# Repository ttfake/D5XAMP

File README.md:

Non Inverting Amplifier with selectable feedback resistors and indicator light

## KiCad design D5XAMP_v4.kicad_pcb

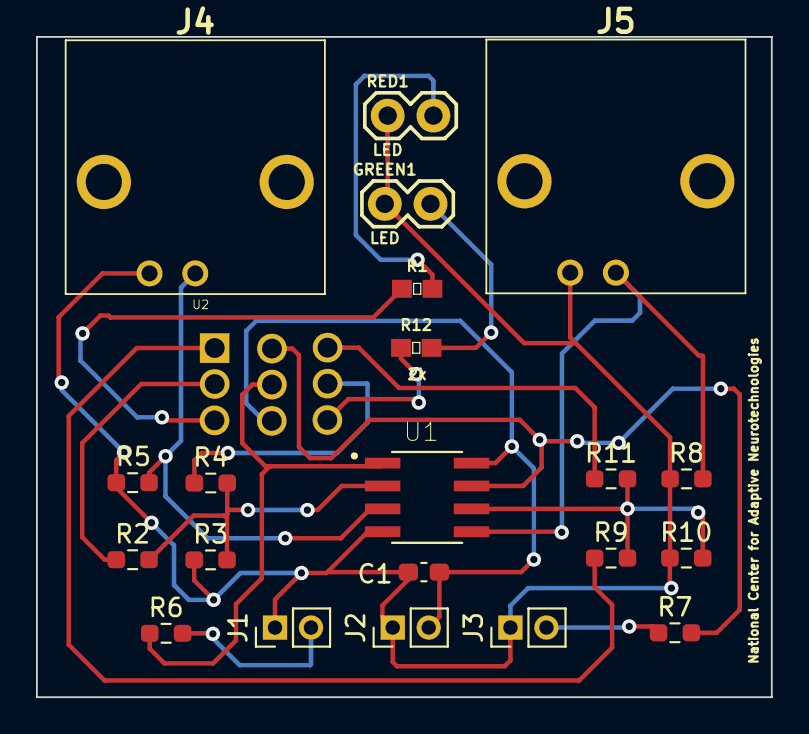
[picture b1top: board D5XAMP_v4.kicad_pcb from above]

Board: 2 copper layers, 40.8 x 36.7 mm, 22 parts (0 on the bottom side), 18 nets.

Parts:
C1: 0.1u; C_0603_1608Metric_Pad1.08x0.95mm_HandSolder
GREEN1: LED; 1X02
J1: Output 1; PinHeader_1x02_P2.00mm_Vertical
J2: PWR; PinHeader_1x02_P2.00mm_Vertical
J3: Output 2; PinHeader_1x02_P2.00mm_Vertical
J4, J5: Conn_Coaxial; 031543110RFX
R1, R12: 2k; 0603
R2, R9: 100k; R_0603_1608Metric_Pad0.98x0.95mm_HandSolder
R3, R10: 20k; R_0603_1608Metric_Pad0.98x0.95mm_HandSolder
R4, R11: 140k; R_0603_1608Metric_Pad0.98x0.95mm_HandSolder
R5, R8: 17.4k; R_0603_1608Metric_Pad0.98x0.95mm_HandSolder
R6, R7: 52.2; R_0603_1608Metric_Pad0.98x0.95mm_HandSolder
RED1: LED; 1X02
U1: NCV33072ADR2G; SOIC127P599X175-8N
U2: SW_3PDT_Standard; SW_1-1437575-7

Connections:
GND: C1.1, GREEN1.1 (K), J1.1, J2.1, J3.1, J4.1 (In), J5.1 (In), R3.1, R5.2, R8.1, R10.1, RED1.1 (K), U1.4 (VEE)
GREEN: R12.1, U2.9 (6)
Input 1: J4.2 (Ext), R5.1, U1.3 (+input1)
Input 2: J5.2 (Ext), R8.2, U1.5 (+input2)
unnamed: GREEN1.2 (A), R12.2
unnamed: R2.1, U2.5
unnamed: R2.2, R3.2, R4.2, U1.2 (-input1)
unnamed: R4.1, U2.6
unnamed: R6.1, U1.1 (Output1), U2.4
unnamed: R7.2, U1.7 (Output2), U2.1
unnamed: R9.1, U2.2
unnamed: R9.2, R10.2, R11.2, U1.6 (-input2)
unnamed: R11.1, U2.3
unnamed: R1.2, RED1.2 (A)
Output 1: J1.2, R6.2
Output 2: J3.2, R7.1
PWR: C1.2, J2.2, U1.8 (VCC), U2.7 (4)
RED: R1.1, U2.8 (5)
